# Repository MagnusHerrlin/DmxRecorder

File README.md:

# DmxRecorder
ArtNet and Dmx Recorder/Player for RaspberryPi using Node Js
or rather a Node Js wrapper for ola-recorder and some different shell scripts?

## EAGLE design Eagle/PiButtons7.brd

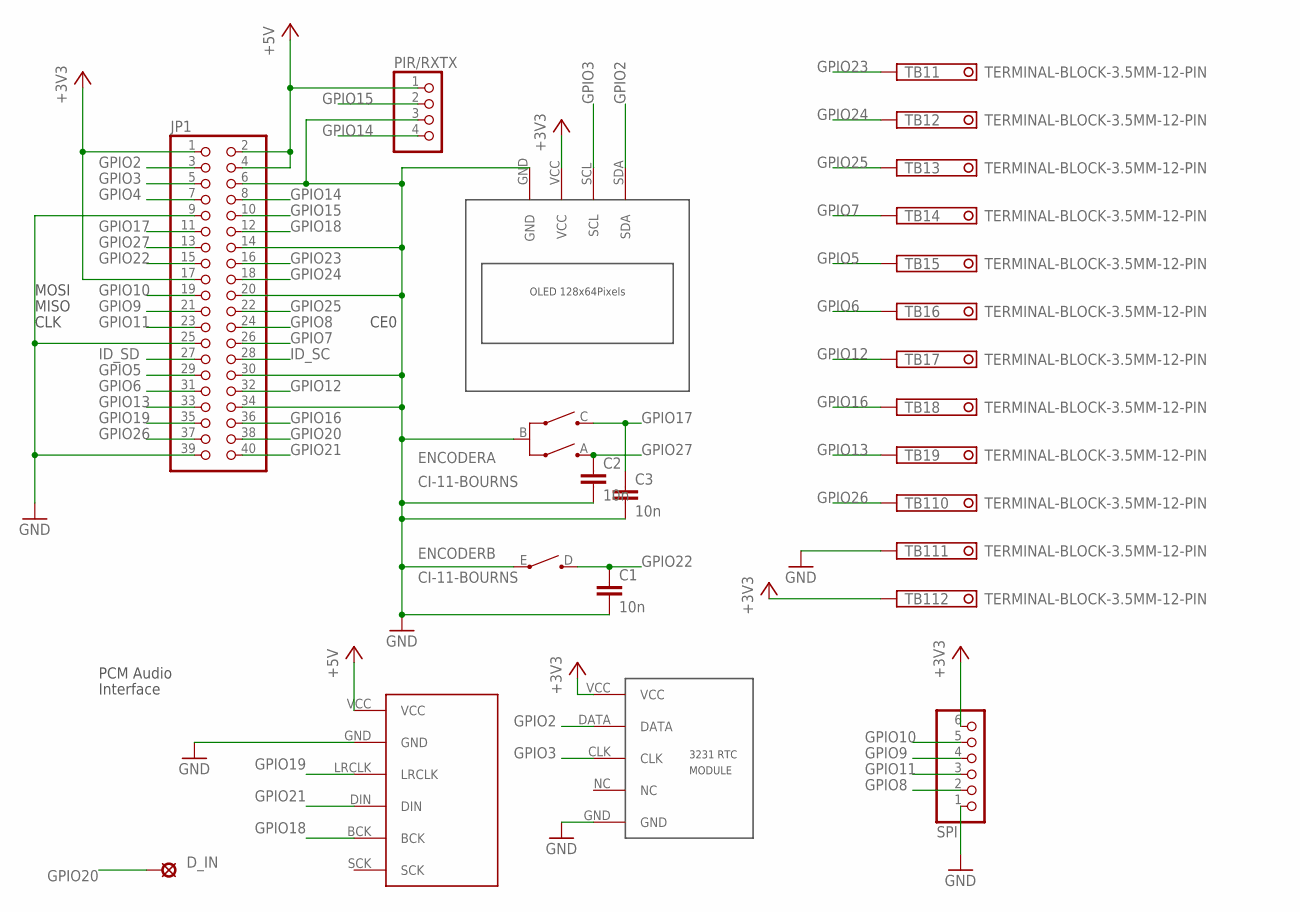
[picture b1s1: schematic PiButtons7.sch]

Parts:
C1, C2, C3: 10n; C050-025X075
D_IN: LSP10
ENCODER: CI-11-BOURNS; CI-11
JP1: PINHD-2X20; 2X20
PIR/RXTX: PINHD-1X4; 1X04
SPI: PINHD-1X6; 1X06
TB1: TERMINAL-BLOCK-3.5MM-12-PIN; TERMINAL-BLOCK-12-PIN-3.5MM-LONG-PAD
U$1: PCM5102CARDPCB; PCM5102CARD
U$2: OLEDI2CDISPLAY; OLEDI2C
U$3: RTC3231PCB

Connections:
+3V3: JP1.1, JP1.17, SPI.6, TB1.12, U$2.VCC, U$3.VCC
+5V: JP1.2, JP1.4, PIR/RXTX.1, U$1.VCC
GND: C1.2, C2.2, C3.2, ENCODER.B (C), ENCODER.E, JP1.6, JP1.9, JP1.14, JP1.20, JP1.25, JP1.30, JP1.34, JP1.39, PIR/RXTX.3, SPI.1, TB1.11, U$1.GND, U$2.GND, U$3.GND
GPIO2: JP1.3, U$2.SDA, U$3.DATA
GPIO3: JP1.5, U$2.SCL, U$3.CLK
GPIO4: JP1.7
GPIO5: JP1.29, TB1.5
GPIO6: JP1.31, TB1.6
GPIO7: JP1.26, TB1.4
GPIO8: JP1.24, SPI.2
GPIO9: JP1.21, SPI.4
GPIO10: JP1.19, SPI.5
GPIO11: JP1.23, SPI.3
GPIO12: JP1.32, TB1.7
GPIO13: JP1.33, TB1.9
GPIO14: JP1.8, PIR/RXTX.4
GPIO15: JP1.10, PIR/RXTX.2
GPIO16: JP1.36, TB1.8
GPIO17: C3.1, ENCODER.C (B), JP1.11
GPIO18: JP1.12, U$1.BCK
GPIO19: JP1.35, U$1.LRCLK
GPIO20: D_IN.MP, JP1.38
GPIO21: JP1.40, U$1.DIN
GPIO22: C1.1, ENCODER.D, JP1.15
GPIO23: JP1.16, TB1.1
GPIO24: JP1.18, TB1.2
GPIO25: JP1.22, TB1.3
GPIO26: JP1.37, TB1.10
GPIO27: C2.1, ENCODER.A, JP1.13
ID_SC: JP1.28
ID_SD: JP1.27

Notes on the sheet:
PCM Audio
Interface
MOSI
MISO
CLK
CE0

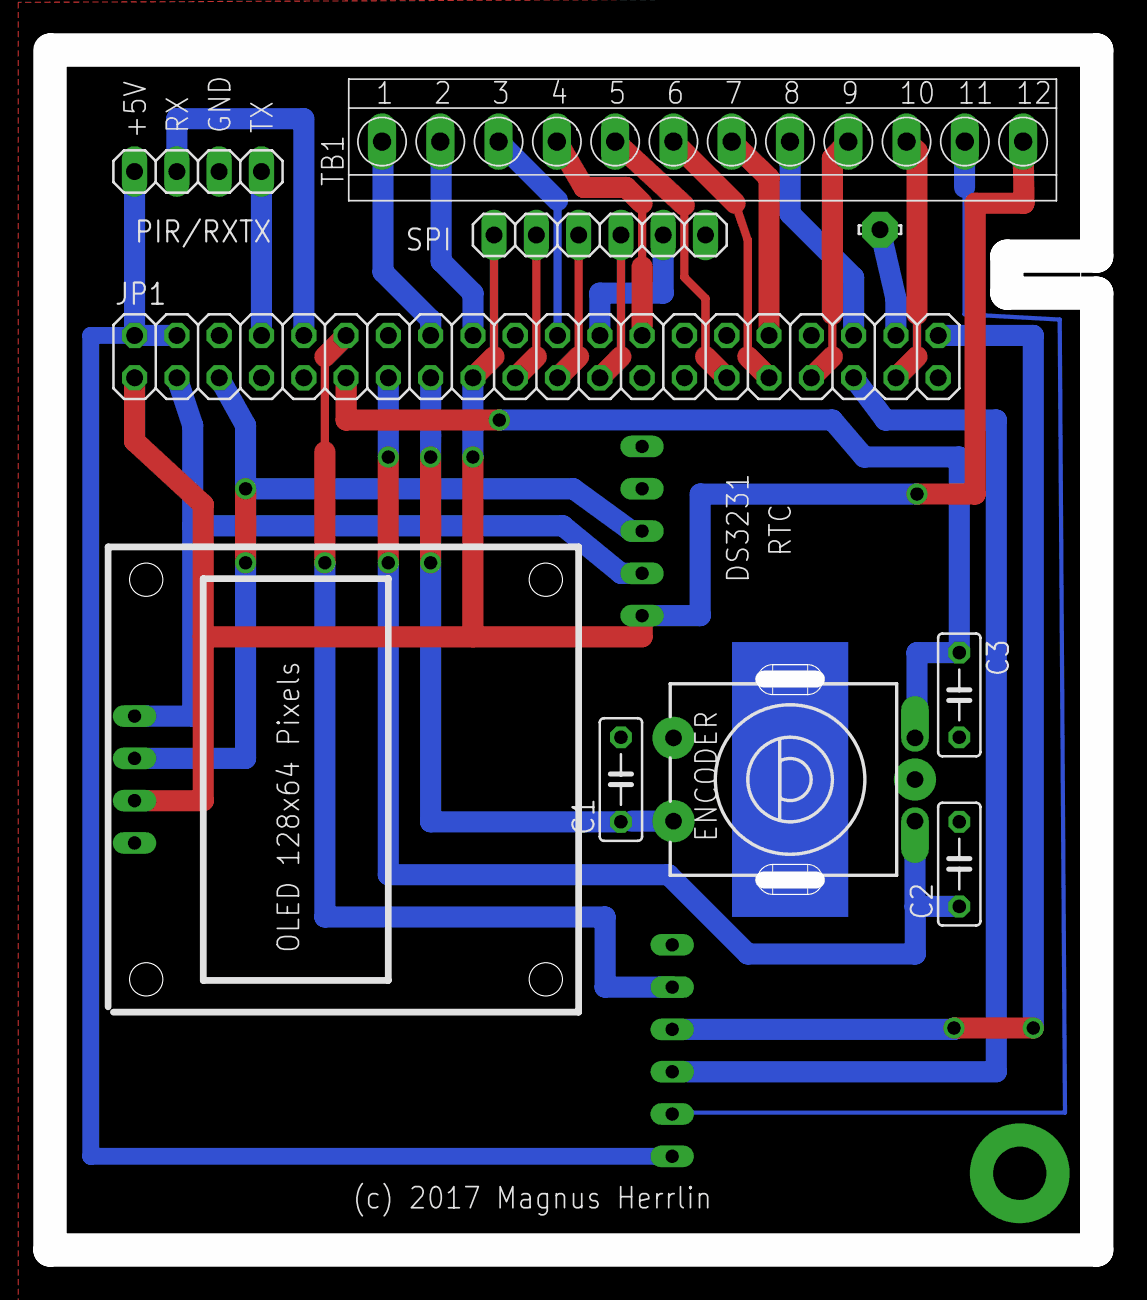
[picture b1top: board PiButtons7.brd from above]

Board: 2 copper layers, 62.9 x 72.1 mm, 12 parts (0 on the bottom side), 28 nets.

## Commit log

2019-11-03 Create EagleCad Files
2019-11-03 Add files via upload
    This is the EagleCadfiles for the Rpi Hat I made

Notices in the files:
Eagle/PiButtons7.brd:
(c) 2017 Magnus Herrlin
